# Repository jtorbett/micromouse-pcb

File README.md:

# Micromouse code

*A maze-solving micromouse implemented on STM32F446RE*

This mouse design has two DC motors driven by a TI DRV8833, and 4 IR sensors, two looking forward at an outward angle and two looking sideways, again at an angle.
Odometry is provided by a hall effect quadrature encoder on each motor.
Provision is made for a TDK ICM-42688 IMU, or a TDK ICM-45688 if and when that becomes available.
A forward-facing VL53L4CD time-of-flight ranging sensor is used for look-ahead

## Pin Descriptions

| STM32F446RE Pin number | Configuration | Name | Description |
|------------|---------------|----------|-------------|
| | PWM Output | LMotor_A | Left motor PWM signal 1 |
| | PWM Output | LMotor_B | Left motor PWM signal 2 |
| | PWM Output | RMotor_A | Right motor PWM signal 1 |
| | PWM Output | RMotor_B | Right motor PWM signal 2 |
| | GPIO Output | Motors_EN | DRM8833 Enable line |
| | GPIO Output | IR_Front_L_Pulse | Front left IR emitter pulse enable |
| | GPIO Output | IR_Front_R_Pulse | Front right IR emitter pulse enable |
| | GPIO Output | IR_L_Pulse | Left IR emitter pulse enable |
| | GPIO Output | IR_R_Pulse | Right IR emitter pulse enable |
| | ADC | IR_Front_L | Front Left IR Sensor |
| | ADC | IR_Front_R | Front Right IR Sensor |
| | ADC | IR_L | Left IR Sensor |
| | ADC | IR_R | Right IR Sensor |
| | Interrupt Input | L_ENC_A | Left encoder channel A |
| | Interrupt Input | L_ENC_B | Left encoder channel B |
| | Interrupt Input | R_ENC_A | Right encoder channel A |
| | Interrupt Input | R_ENC_B | Right encoder channel B |
| | I2C SDA | VL53L4CD_SDA | I2C bus data for VL53L4CD |
| | I2C SCL | VL53L4CD_SCL | I2C bus clock for VL53L4CD |
| | Interrupt Input | VL53L4CD_INT | Interrupt from VL53L4CD |
| | GPIO Output | VL53L4CD_EN | Enable for VL53L4CD |
| | SPI SCK | ICM-42688_SCK | SPI Clock for ICM-42688 |
| | SPI MISO | ICM-42688_MISO | SPI MISO for ICM-42688 |
| | SPI MOSI | ICM-42688_MOSI | SPI MOSI for ICM-42688 |
| | SPI CS or GPIO Output | ICM-42688_CS | Chip select, active low, for ICM-42688 |
| | GPIO Interrupt | ICM-42688_INT1 | Interrupt 1 from ICM-42688 |
| | GPIO Interrupt | ICM-42688_INT2 | Interrupt 2 from ICM-42688 |
| | GPIO Input or Interrupt | SW1 | Switch 1, momentary push-button input |
| | GPIO Input or Interrupt | SW2 | Switch 2, momentary push-button input |
| | GPIO Output | LED1 | LED 1 Output |
| | GPIO Output | LED2 | LED 2 Output |
| | ADC | VBATT | Battery voltage input |
| | SWDIO | SWDIO | Serial Wire Debug Data |
| | SWDCLK | SWDCLK | Serial Wire Debug Clock |

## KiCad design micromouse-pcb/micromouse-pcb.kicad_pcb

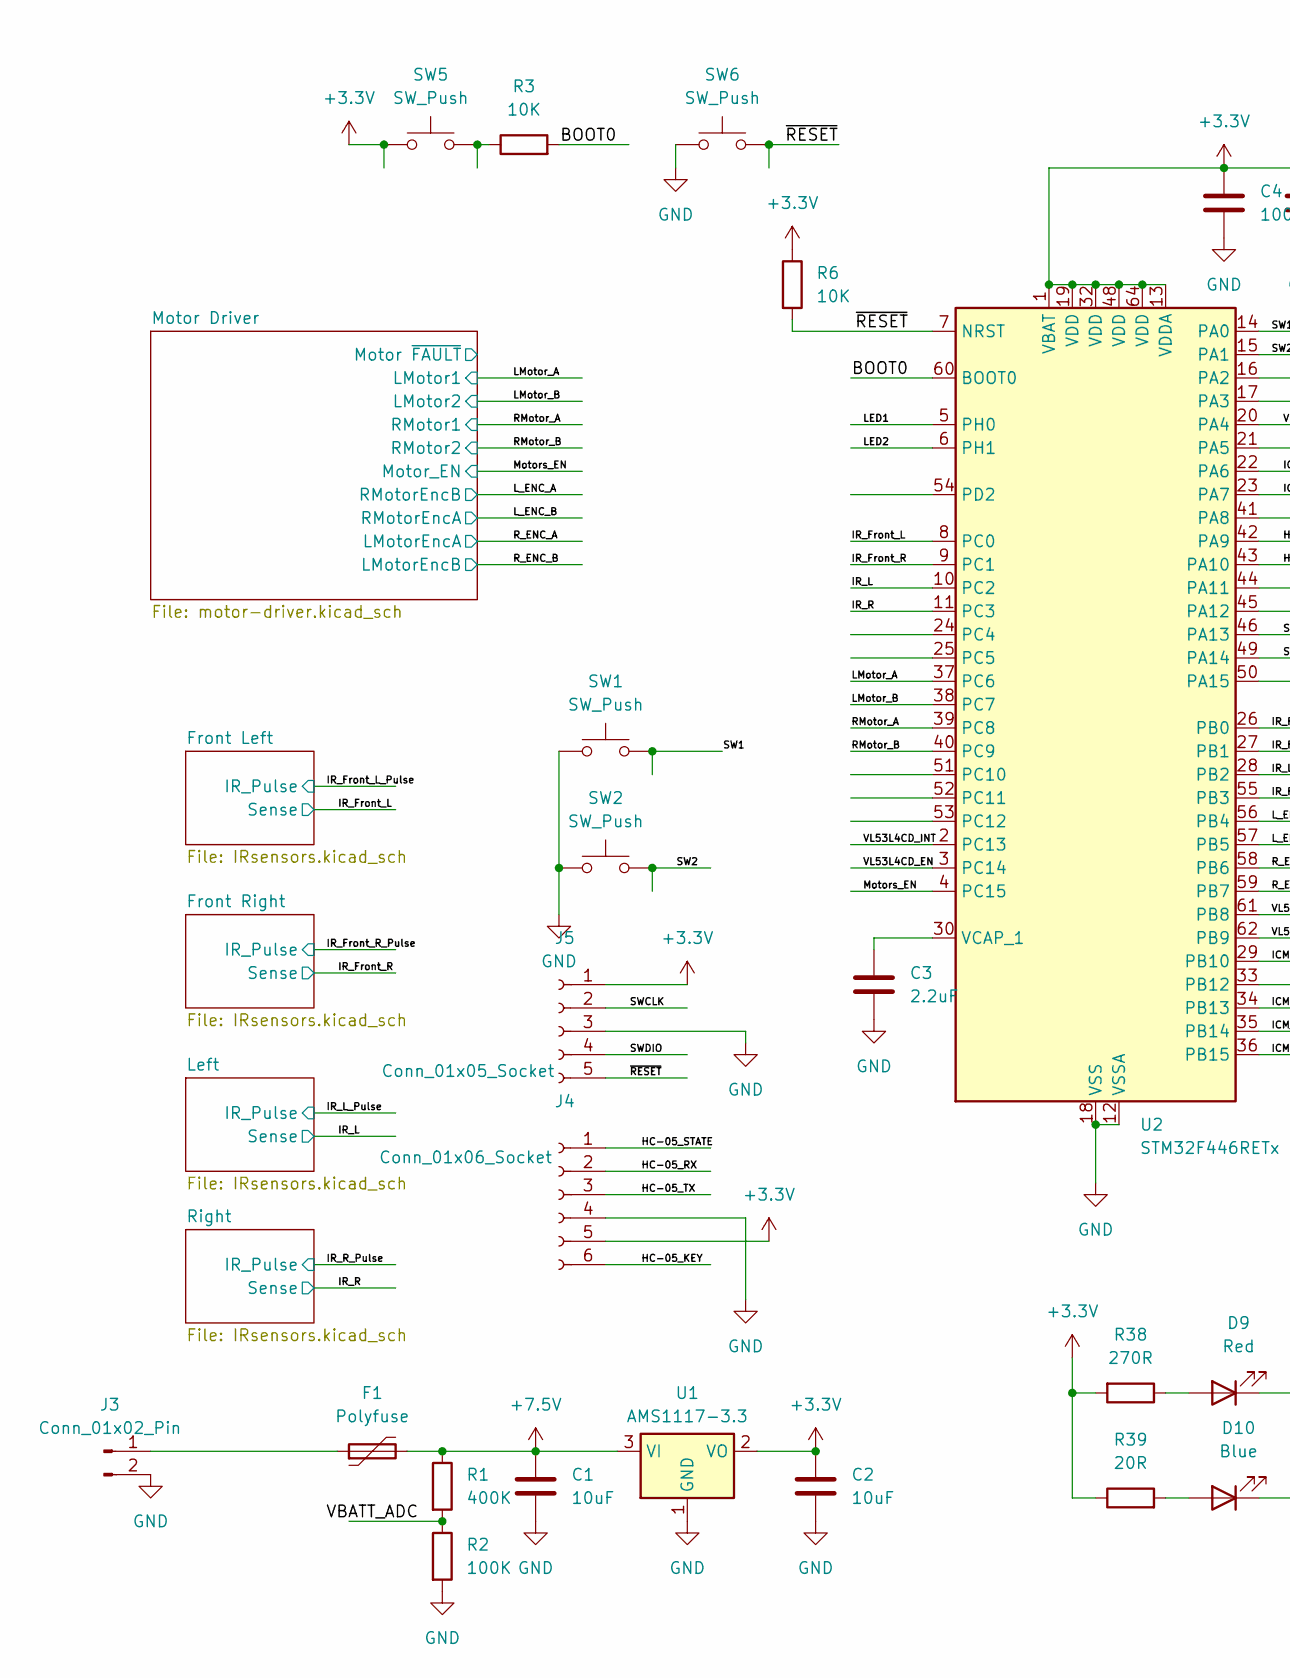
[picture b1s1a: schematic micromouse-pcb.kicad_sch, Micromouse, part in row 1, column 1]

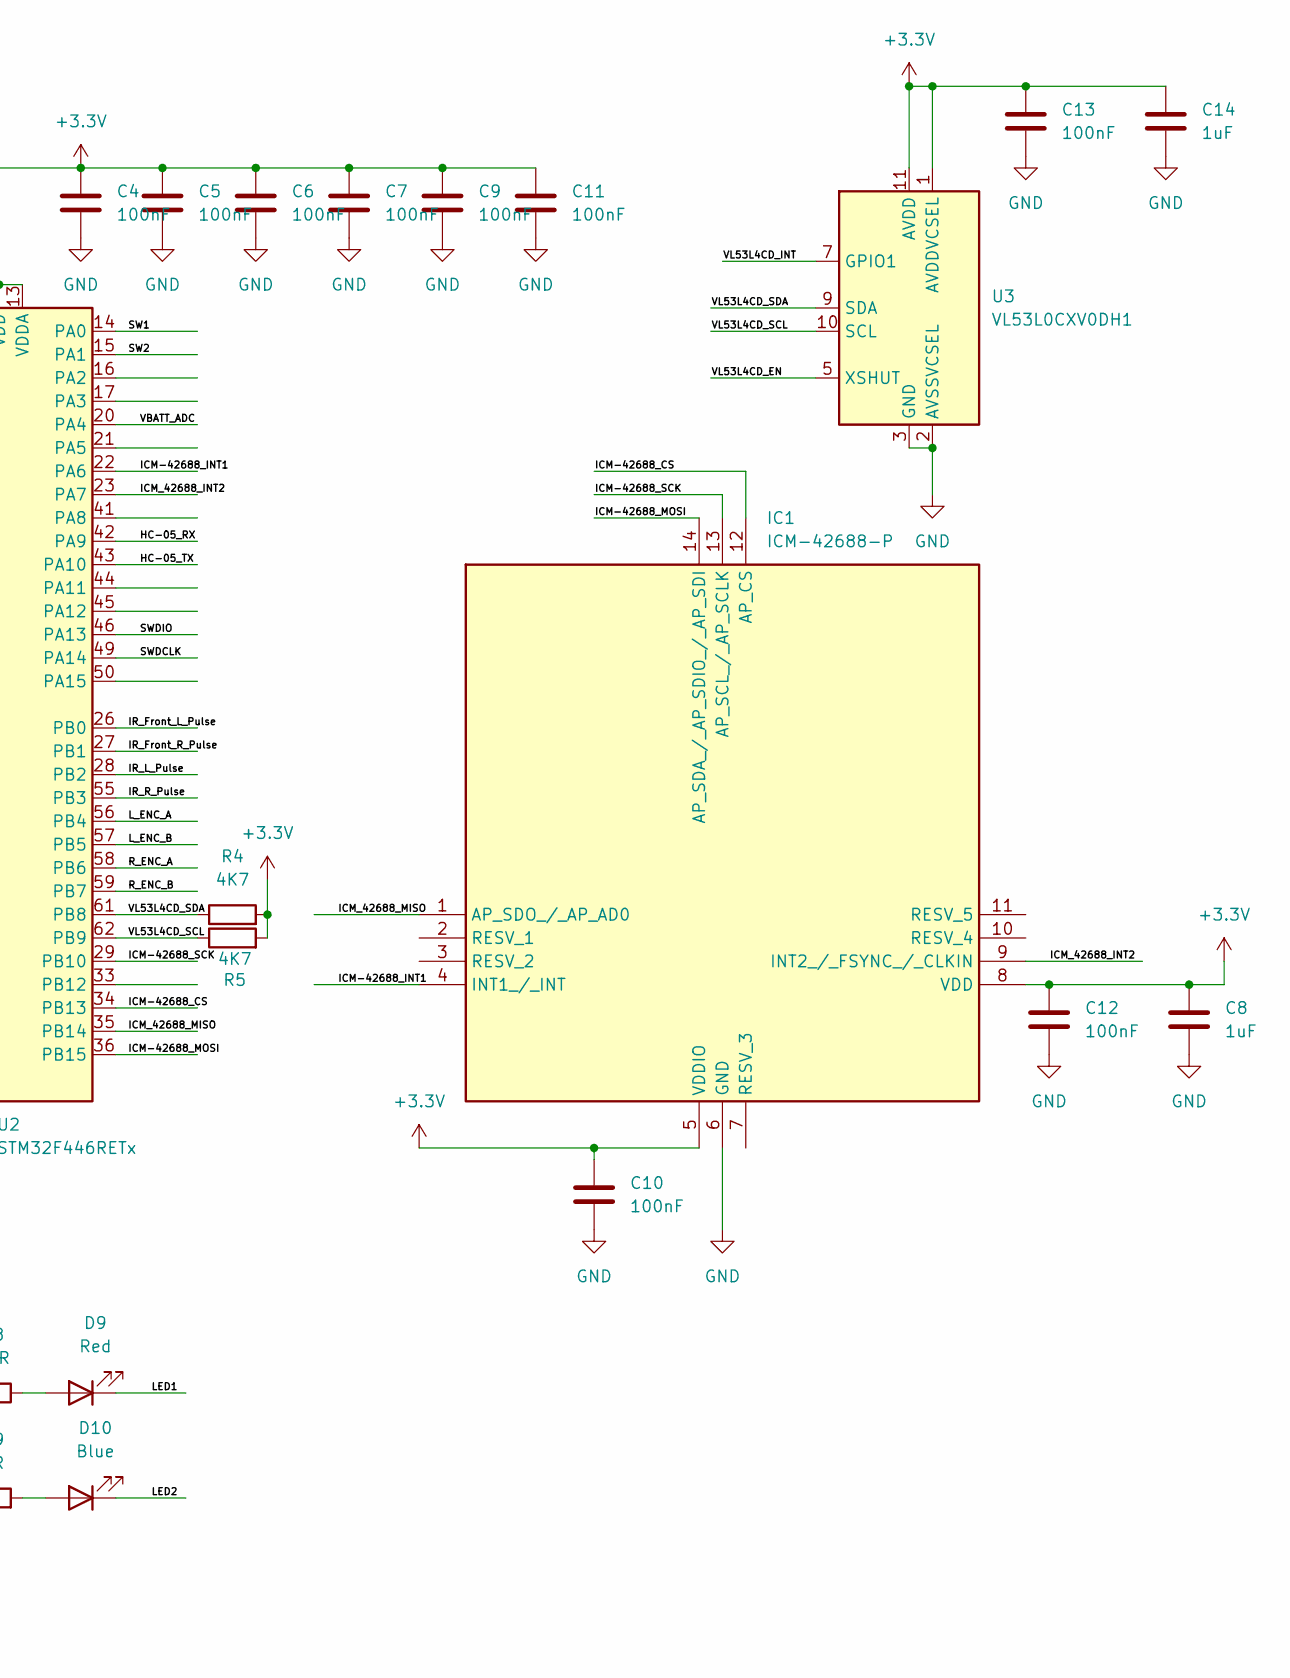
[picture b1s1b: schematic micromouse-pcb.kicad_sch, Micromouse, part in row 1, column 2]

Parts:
C1, C2: 10uF; C_1210_3225Metric
C3: 2.2uF; C_1210_3225Metric
C4, C5, C6, C7, C9, C11, C12, C13: 100nF; C_0603_1608Metric
C8: 1uF; C_0603_1608Metric
C10: 100nF; C_0805_2012Metric
C14: 1uF; C_0805_2012Metric
D9: Red; LED_0603_1608Metric
D10: Blue; LED_0603_1608Metric
F1: Polyfuse; Fuse_1210_3225Metric
IC1: ICM-42688-P; IIM42352; Mouser Part Number 410-ICM-42688-P
J3: Conn_01x02_Pin; JST_EH_B2B-EH-A_1x02_P2.50mm_Vertical
J4: Conn_01x06_Socket; PinSocket_1x06_P2.54mm_Vertical
J5: Conn_01x05_Socket; PinHeader_1x05_P2.54mm_Vertical
R1: 400K; R_0603_1608Metric
R2: 100K; R_0603_1608Metric
R3, R6: 10K; R_0603_1608Metric
R4, R5: 4K7; R_0603_1608Metric
R38: 270R; R_0603_1608Metric_Pad0.98x0.95mm_HandSolder
R39: 20R; R_0603_1608Metric
SW1, SW2, SW5, SW6: SW_Push; SW_Push_1P1T_NO_CK_KSC6xxJ
U1: AMS1117-3.3; SOT-223-3_TabPin2
U2: STM32F446RETx; LQFP-64_10x10mm_P0.5mm
U3: VL53L0CXV0DH1; ST_VL53L1x

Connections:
+3.3V: C2.1, C4.1, C5.1, C6.1, C7.1, C8.1, C9.1, C10.1, C11.1, C12.1, C13.1, C14.1, IC1.5 (VDDIO), IC1.8 (VDD), J4.5, J5.1, R4.2, R5.2, R6.1, R38.2, R39.1, SW5.1, U1.2 (VO), U2.1 (VBAT), U2.13 (VDDA), U2.19 (VDD), U2.32 (VDD), U2.48 (VDD), U2.64 (VDD), U3.1 (AVDDVCSEL), U3.11 (AVDD); also elsewhere on the board
+7.5V: C1.1, F1.2, R1.1, U1.3 (VI); also elsewhere on the board
/BOOT0: R3.2, U2.60 (BOOT0)
/HC-05_KEY: J4.6
/HC-05_RX: J4.2, U2.42 (PA9)
/HC-05_STATE: J4.1
/HC-05_TX: J4.3, U2.43 (PA10)
/ICM-42688_CS: IC1.12 (AP_CS), U2.34 (PB13)
/ICM-42688_INT1: IC1.4 (INT1_/_INT), U2.22 (PA6)
/ICM-42688_MOSI: IC1.14 (AP_SDA_/_AP_SDIO_/_AP_SDI), U2.36 (PB15)
/ICM-42688_SCK: IC1.13 (AP_SCL_/_AP_SCLK), U2.29 (PB10)
/ICM_42688_INT2: IC1.9 (INT2_/_FSYNC_/_CLKIN), U2.23 (PA7)
/ICM_42688_MISO: IC1.1 (AP_SDO_/_AP_AD0), U2.35 (PB14)
/IR_Front_L: U2.8 (PC0); also elsewhere on the board
/IR_Front_L_Pulse: U2.26 (PB0); also elsewhere on the board
/IR_Front_R: U2.9 (PC1); also elsewhere on the board
/IR_Front_R_Pulse: U2.27 (PB1); also elsewhere on the board
/IR_L: U2.10 (PC2); also elsewhere on the board
/IR_L_Pulse: U2.28 (PB2); also elsewhere on the board
/IR_R: U2.11 (PC3); also elsewhere on the board
/IR_R_Pulse: U2.55 (PB3); also elsewhere on the board
/LED1: D9.1 (K), U2.5 (PH0)
/LED2: D10.1 (K), U2.6 (PH1)
/LMotor_A: U2.37 (PC6); also elsewhere on the board
/LMotor_B: U2.38 (PC7); also elsewhere on the board
/L_ENC_A: U2.56 (PB4); also elsewhere on the board
/L_ENC_B: U2.57 (PB5); also elsewhere on the board
/Motors_EN: U2.4 (PC15); also elsewhere on the board
/RMotor_A: U2.39 (PC8); also elsewhere on the board
/RMotor_B: U2.40 (PC9); also elsewhere on the board
/R_ENC_A: U2.58 (PB6); also elsewhere on the board
/R_ENC_B: U2.59 (PB7); also elsewhere on the board
/SW1: SW1.2, U2.14 (PA0)
/SW2: SW2.2, U2.15 (PA1)
/SWCLK: J5.2
/SWDCLK: U2.49 (PA14)
/SWDIO: J5.4, U2.46 (PA13)
/VBATT_ADC: R1.2, R2.1, U2.20 (PA4)
/VL53L4CD_EN: U2.3 (PC14), U3.5 (XSHUT)
/VL53L4CD_INT: U2.2 (PC13), U3.7 (GPIO1)
/VL53L4CD_SCL: R5.1, U2.62 (PB9), U3.10 (SCL)
/VL53L4CD_SDA: R4.1, U2.61 (PB8), U3.9 (SDA)
/~RESET: J5.5, R6.2, SW6.2, U2.7 (NRST)
GND: C1.2, C2.2, C3.2, C4.2, C5.2, C6.2, C7.2, C8.2, C9.2, C10.2, C11.2, C12.2, C13.2, C14.2, IC1.6 (GND), J3.2, J4.4, J5.3, R2.2, SW1.1, SW2.1, SW6.1, U1.1 (GND), U2.12 (VSSA), U2.18 (VSS), U2.31 (VSS), U2.47 (VSS), U2.63 (VSS), U3.2 (AVSSVCSEL), U3.3 (GND), U3.4 (GND), U3.6 (GND), U3.12 (GND); also elsewhere on the board
unnamed: D9.2 (A), R38.1
unnamed: D10.2 (A), R39.2
unnamed: F1.1, J3.1
unnamed: R3.1, SW5.2
unnamed: C3.1, U2.30 (VCAP_1)

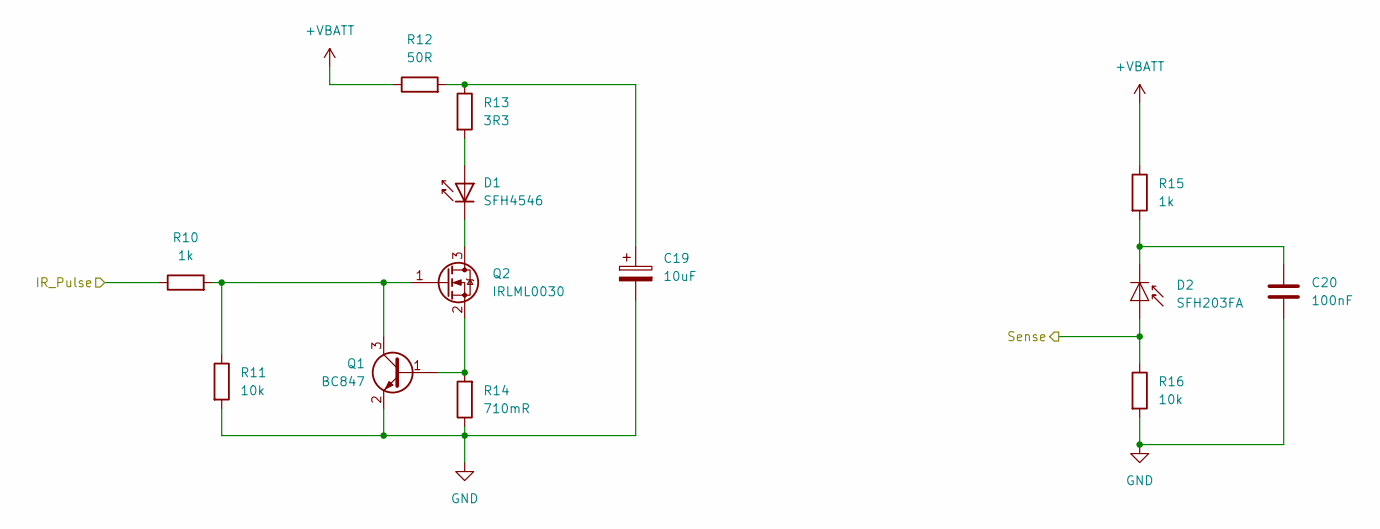
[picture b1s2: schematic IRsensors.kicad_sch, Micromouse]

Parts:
C19: 10uF; CP_Elec_6.3x4.5
C20: 100nF; C_0603_1608Metric
D1: SFH4546; LED_D5.0mm_IRGrey
D2: SFH203FA; LED_D5.0mm_IRGrey
Q1: BC847; SOT-23
Q2: IRLML0030; SOT-23
R10: 1k; R_0603_1608Metric
R11, R16: 10k; R_0603_1608Metric
R12: 50R; R_1206_3216Metric
R13: 3R3; R_1206_3216Metric
R14: 710mR; R_1206_3216Metric
R15: 1k; R_0805_2012Metric

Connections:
+VBATT: R12.1, R15.1; also elsewhere on the board
/IR_Front_R: D2.2 (A), R16.1; also elsewhere on the board
/IR_Front_R_Pulse: R10.1; also elsewhere on the board
GND: C19.2, C20.2, Q1.2 (E), R11.2, R14.1, R16.2; also elsewhere on the board
unnamed: C19.1, R12.2, R13.1
unnamed: D1.2 (A), R13.2
unnamed: D1.1 (K), Q2.3 (D)
unnamed: C20.1, D2.1 (K), R15.2
unnamed: Q1.1 (B), Q2.2 (S), R14.2
unnamed: Q1.3 (C), Q2.1 (G), R10.2, R11.1

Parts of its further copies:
C21, C23, C25: 10uF; CP_Elec_6.3x4.5
C22, C24, C26: 100nF; C_0603_1608Metric
D3, D5, D7: SFH4546; LED_D5.0mm_IRGrey
D4, D6, D8: SFH203FA; LED_D5.0mm_IRGrey
Q3, Q5, Q7: BC847; SOT-23
Q4, Q6, Q8: IRLML0030; SOT-23
R17, R24, R31: 1k; R_0603_1608Metric
R18, R23, R25, R30, R32, R37: 10k; R_0603_1608Metric
R19, R26, R33: 50R; R_1206_3216Metric
R20, R27, R34: 3R3; R_1206_3216Metric
R21, R28, R35: 710mR; R_1206_3216Metric
R22, R29, R36: 1k; R_0805_2012Metric

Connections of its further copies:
+VBATT: R19.1, R22.1, R26.1, R29.1, R33.1, R36.1; also elsewhere on the board
/IR_Front_L: D6.2 (A), R30.1; also elsewhere on the board
/IR_Front_L_Pulse: R24.1; also elsewhere on the board
/IR_L: D4.2 (A), R23.1; also elsewhere on the board
/IR_L_Pulse: R17.1; also elsewhere on the board
/IR_R: D8.2 (A), R37.1; also elsewhere on the board
/IR_R_Pulse: R31.1; also elsewhere on the board
GND: C21.2, C22.2, C23.2, C24.2, C25.2, C26.2, Q3.2 (E), Q5.2 (E), Q7.2 (E), R18.2, R21.1, R23.2, R25.2, R28.1, R30.2, R32.2, R35.1, R37.2; also elsewhere on the board
unnamed: C21.1, R19.2, R20.1
unnamed: C23.1, R26.2, R27.1
unnamed: C25.1, R33.2, R34.1
unnamed: D3.2 (A), R20.2
unnamed: D3.1 (K), Q4.3 (D)
unnamed: C22.1, D4.1 (K), R22.2
unnamed: D5.2 (A), R27.2
unnamed: D5.1 (K), Q6.3 (D)
unnamed: C24.1, D6.1 (K), R29.2
unnamed: D7.2 (A), R34.2
unnamed: D7.1 (K), Q8.3 (D)
unnamed: C26.1, D8.1 (K), R36.2
unnamed: Q3.1 (B), Q4.2 (S), R21.2
unnamed: Q3.3 (C), Q4.1 (G), R17.2, R18.1
unnamed: Q5.1 (B), Q6.2 (S), R28.2
unnamed: Q5.3 (C), Q6.1 (G), R24.2, R25.1
unnamed: Q7.1 (B), Q8.2 (S), R35.2
unnamed: Q7.3 (C), Q8.1 (G), R31.2, R32.1

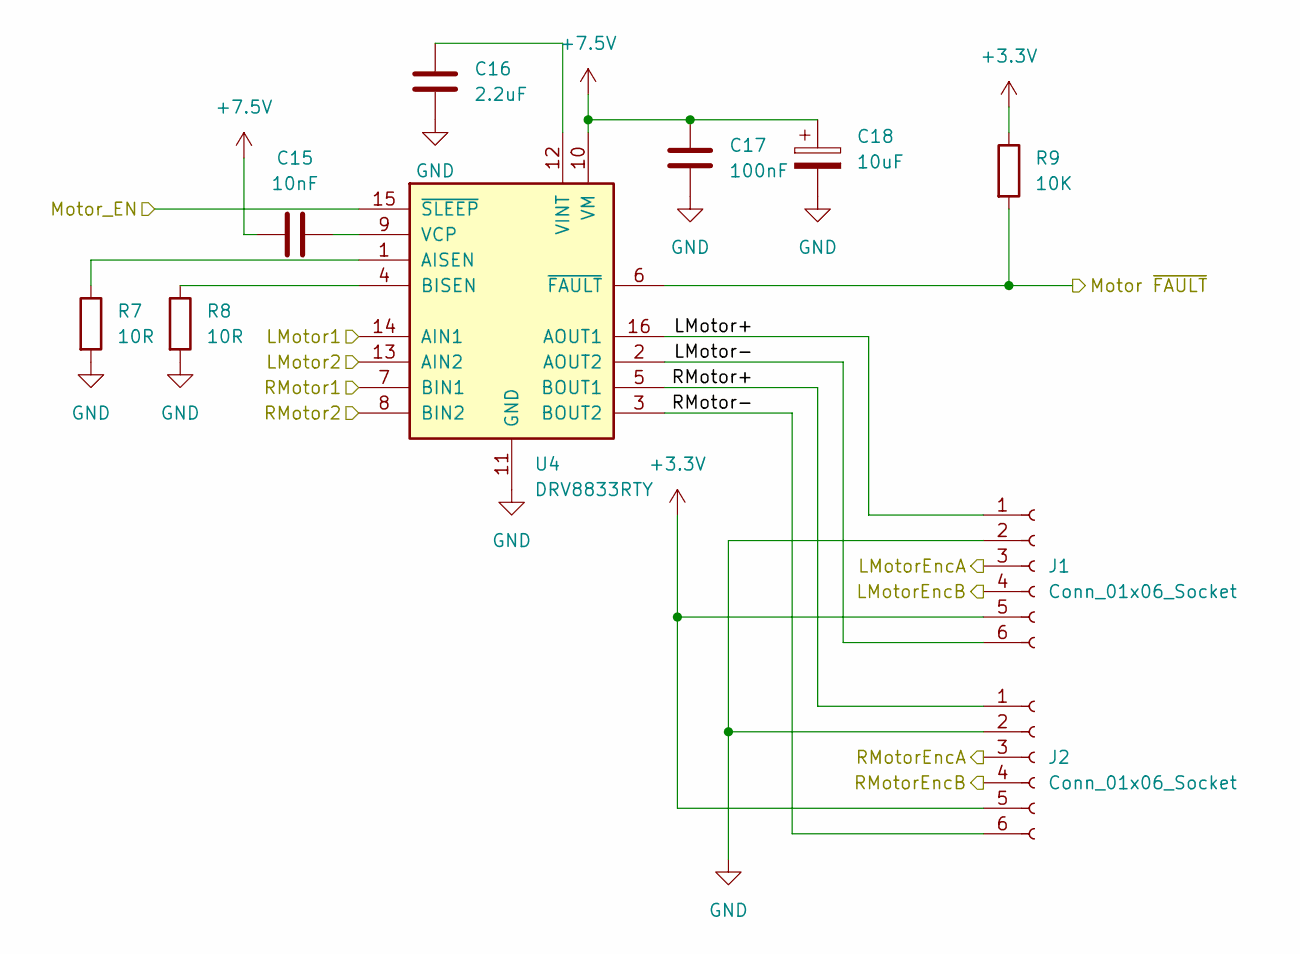
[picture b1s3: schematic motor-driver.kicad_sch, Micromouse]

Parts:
C15: 10nF; C_0603_1608Metric
C16: 2.2uF; C_1812_4532Metric
C17: 100nF; C_0603_1608Metric
C18: 10uF; CP_Elec_6.3x4.5
J1, J2: Conn_01x06_Socket; JST_EH_B6B-EH-A_1x06_P2.50mm_Vertical
R7, R8: 10R; R_1206_3216Metric
R9: 10K; R_0603_1608Metric
U4: DRV8833RTY; Texas_RTY_WQFN-16-1EP_4x4mm_P0.65mm_EP2.1x2.1mm_ThermalVias

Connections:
+3.3V: J1.5, J2.5, R9.1; also elsewhere on the board
+7.5V: C15.1, C17.1, C18.1, U4.10 (VM); also elsewhere on the board
/LMotor_A: U4.14 (AIN1); also elsewhere on the board
/LMotor_B: U4.13 (AIN2); also elsewhere on the board
/L_ENC_A: J2.4; also elsewhere on the board
/L_ENC_B: J2.3; also elsewhere on the board
/Motor Driver/LMotor+: J1.1, U4.16 (AOUT1)
/Motor Driver/LMotor-: J1.6, U4.2 (AOUT2)
/Motor Driver/Motor ~FAULT: R9.2, U4.6 (~FAULT)
/Motor Driver/RMotor+: J2.1, U4.5 (BOUT1)
/Motor Driver/RMotor-: J2.6, U4.3 (BOUT2)
/Motors_EN: U4.15 (~SLEEP); also elsewhere on the board
/RMotor_A: U4.7 (BIN1); also elsewhere on the board
/RMotor_B: U4.8 (BIN2); also elsewhere on the board
/R_ENC_A: J1.3; also elsewhere on the board
/R_ENC_B: J1.4; also elsewhere on the board
GND: C16.2, C17.2, C18.2, J1.2, J2.2, R7.2, R8.2, U4.11 (GND), U4.17 (GND); also elsewhere on the board
unnamed: R7.1, U4.1 (AISEN)
unnamed: R8.1, U4.4 (BISEN)
unnamed: C15.2, U4.9 (VCP)
unnamed: C16.1, U4.12 (VINT)

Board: 2 copper layers, 98 parts (0 on the bottom side), 79 nets, no tracks yet.

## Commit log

2024-03-31 Initial commit - basic schematic done but need pin assignments
2024-04-02 Finalised schematic
2024-05-15 Updated schematics and brought in board shape from CAD
2024-06-26 Updated outline and PCB file
